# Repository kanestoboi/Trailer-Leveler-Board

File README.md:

# Trailer Leveler Board
This repository contains the PCB design of the Trailer Leveler project, a wireless trailer leveling system. The firmware for this board and Android application to connect to the device via Bluetooth LE can be found in the [Trailer Leveler Software](https://github.com/kanestoboi/Trailer-Leveler-Software) repository.

Features
* 16 bit, 3 axis accelerometer for precise angle measurement
* Circuity to support over the air (OTA) firmware upload using HM-11 BLE module
* Li-Po battery charging
* Battery overvoltage and undervoltage protection circuitry
* Internal 8 MHz oscillator used for clock to reduce BOM cost and power requirements
* Battery monitoring capability

## Photos
Images of the board can be found in the [images](https://github.com/kanestoboi/Trailer-Leveler-Board/tree/master/images) directory.

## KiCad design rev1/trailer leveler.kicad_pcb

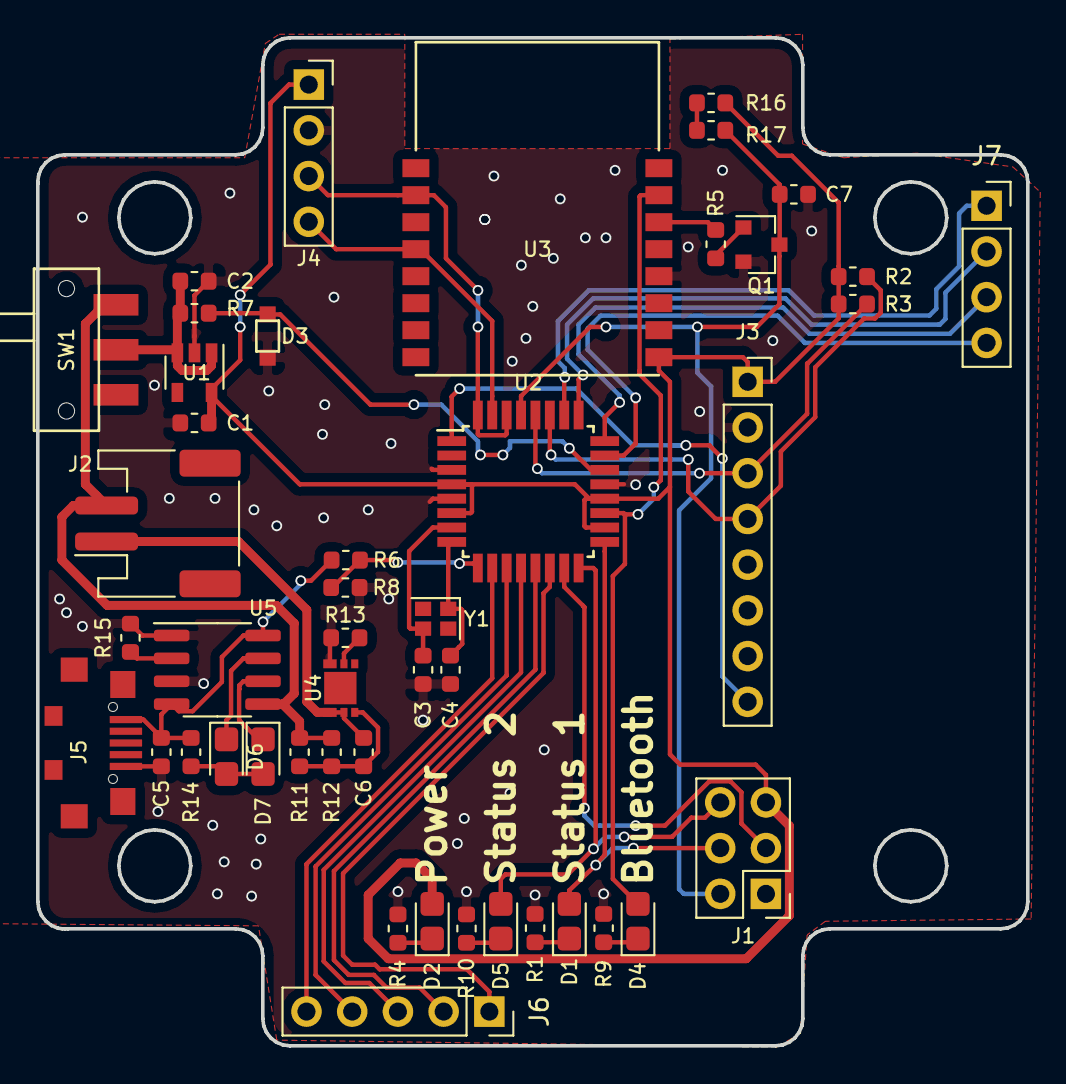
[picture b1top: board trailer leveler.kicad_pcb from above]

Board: 2 copper layers, 55.0 x 56.0 mm, 46 parts (0 on the bottom side), 42 nets.

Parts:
C1, C2, C5, C6, C7: 100nF; C_0603_1608Metric
C3, C4: 10pF; C_0603_1608Metric
D1, D2, D4, D5, D6, D7: LED; LED_0805_2012Metric_Castellated
D3: D_Zener; SC-90A
J1: Conn_02x03_Odd_Even; Pin_Header_Straight_2x03_Pitch2.54mm
J2: Conn_01x02_Female; JST_PH_S2B-PH-SM4-TB_1x02-1MP_P2.00mm_Horizontal
J3: Conn_01x08_Female; PinSocket_1x08_P2.54mm_Vertical
J4: Conn_01x04_Female; PinSocket_1x04_P2.54mm_Vertical
J5: USB_OTG; USB_Micro_C77238
J6: Conn_01x05; PinSocket_1x05_P2.54mm_Vertical
J7: Conn_01x04; PinSocket_1x04_P2.54mm_Vertical
Q1: MMBT3904; SOT-23
R1, R4, R5, R6, R8, R9, R10, R11, R12, R13, R14, R15, R16, R17: 2k; R_0603_1608Metric
R2, R3: 10k; R_0603_1608Metric
R7: 47; R_0603_1608Metric
SW1: SW_SPDT; JS102011SAQN
U1: TLV70233_SOT23-5; SOT-23-5
U2: ATMEGA328P-AU; TQFP-32_7x7mm_Pitch0.8mm
U3: HM-11
U4: AP9211; U-DFN2030-6
U5: TP4056; SOP-8_3.76x4.96mm_P1.27mm
Y1: Crystal_GND24_Small; Crystal_SMD_2016-4Pin_2.0x1.6mm

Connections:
3.3V: C1.1, D2.2, J1.5, J3.1, J4.1, R2.1, R3.1, R16.2, U1.5, U2.4, U2.6, U2.18, U2.20, U3.9
+BATT: J2.2, R11.2, R12.2, SW1.1, U5.5
-BATT: C6.2, J2.1, U4.1, U4.2
BT: D4.2, U2.19, U3.15
BTRX: J4.4, U2.31, U3.4
BTTX: J4.3, U2.30, U2.32, U3.2
GNDD: C1.2, C2.2, C3.2, C4.2, C5.2, C7.2, D3.2, J1.1, J3.2, J4.2, J5.5, Q1.2, R1.1, R4.1, R8.1, R9.1, R10.1, R13.1, R15.1, U1.2, U2.3, U2.5, U2.21, U3.12, U4.6, U5.1, U5.3
MISO: D5.2, J1.6, U2.16
MOSI: J1.3, U2.15
MPU_INT: J3.8, U2.1
unnamed: C3.1, U2.7, Y1.3
unnamed: C4.1, U2.8, Y1.1
unnamed: C6.1, R11.1, R12.1, U4.3
unnamed: D1.1, R1.2
unnamed: D2.1, R4.2
unnamed: D3.1, R7.1, U2.22
unnamed: D4.1, R9.2
unnamed: D5.1, R10.2
unnamed: D6.1, U5.7
unnamed: D6.2, D7.2, R14.1
unnamed: D7.1, U5.6
unnamed: Q1.1, R5.2
unnamed: R5.1, U3.14
unnamed: R6.2, R8.2, U2.9
unnamed: R13.2, U4.5
unnamed: R15.2, U5.2
unnamed: R16.1, R17.2
RST: C7.1, J1.2, Q1.3, R17.1, U2.29
SCK: D1.2, J1.4, U2.17
SCL: J3.3, R3.2, U2.28
SDA: J3.4, R2.2, U2.27
VIN: C2.1, R7.2, SW1.2, U1.1, U1.3
VUSB: C5.1, J5.1, R6.1, R14.2, U5.4, U5.8
pin10: J6.5, U2.10
pin11: J6.4, U2.11
pin12: J6.3, U2.12
pin13: J6.2, U2.13
pin14: J6.1, U2.14
pin23: J7.4, U2.23
pin24: J7.3, U2.24
pin25: J7.2, U2.25
pin26: J7.1, U2.26

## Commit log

2021-02-23 added images
2021-02-23 amended image links
2021-02-23 amended link file extension
